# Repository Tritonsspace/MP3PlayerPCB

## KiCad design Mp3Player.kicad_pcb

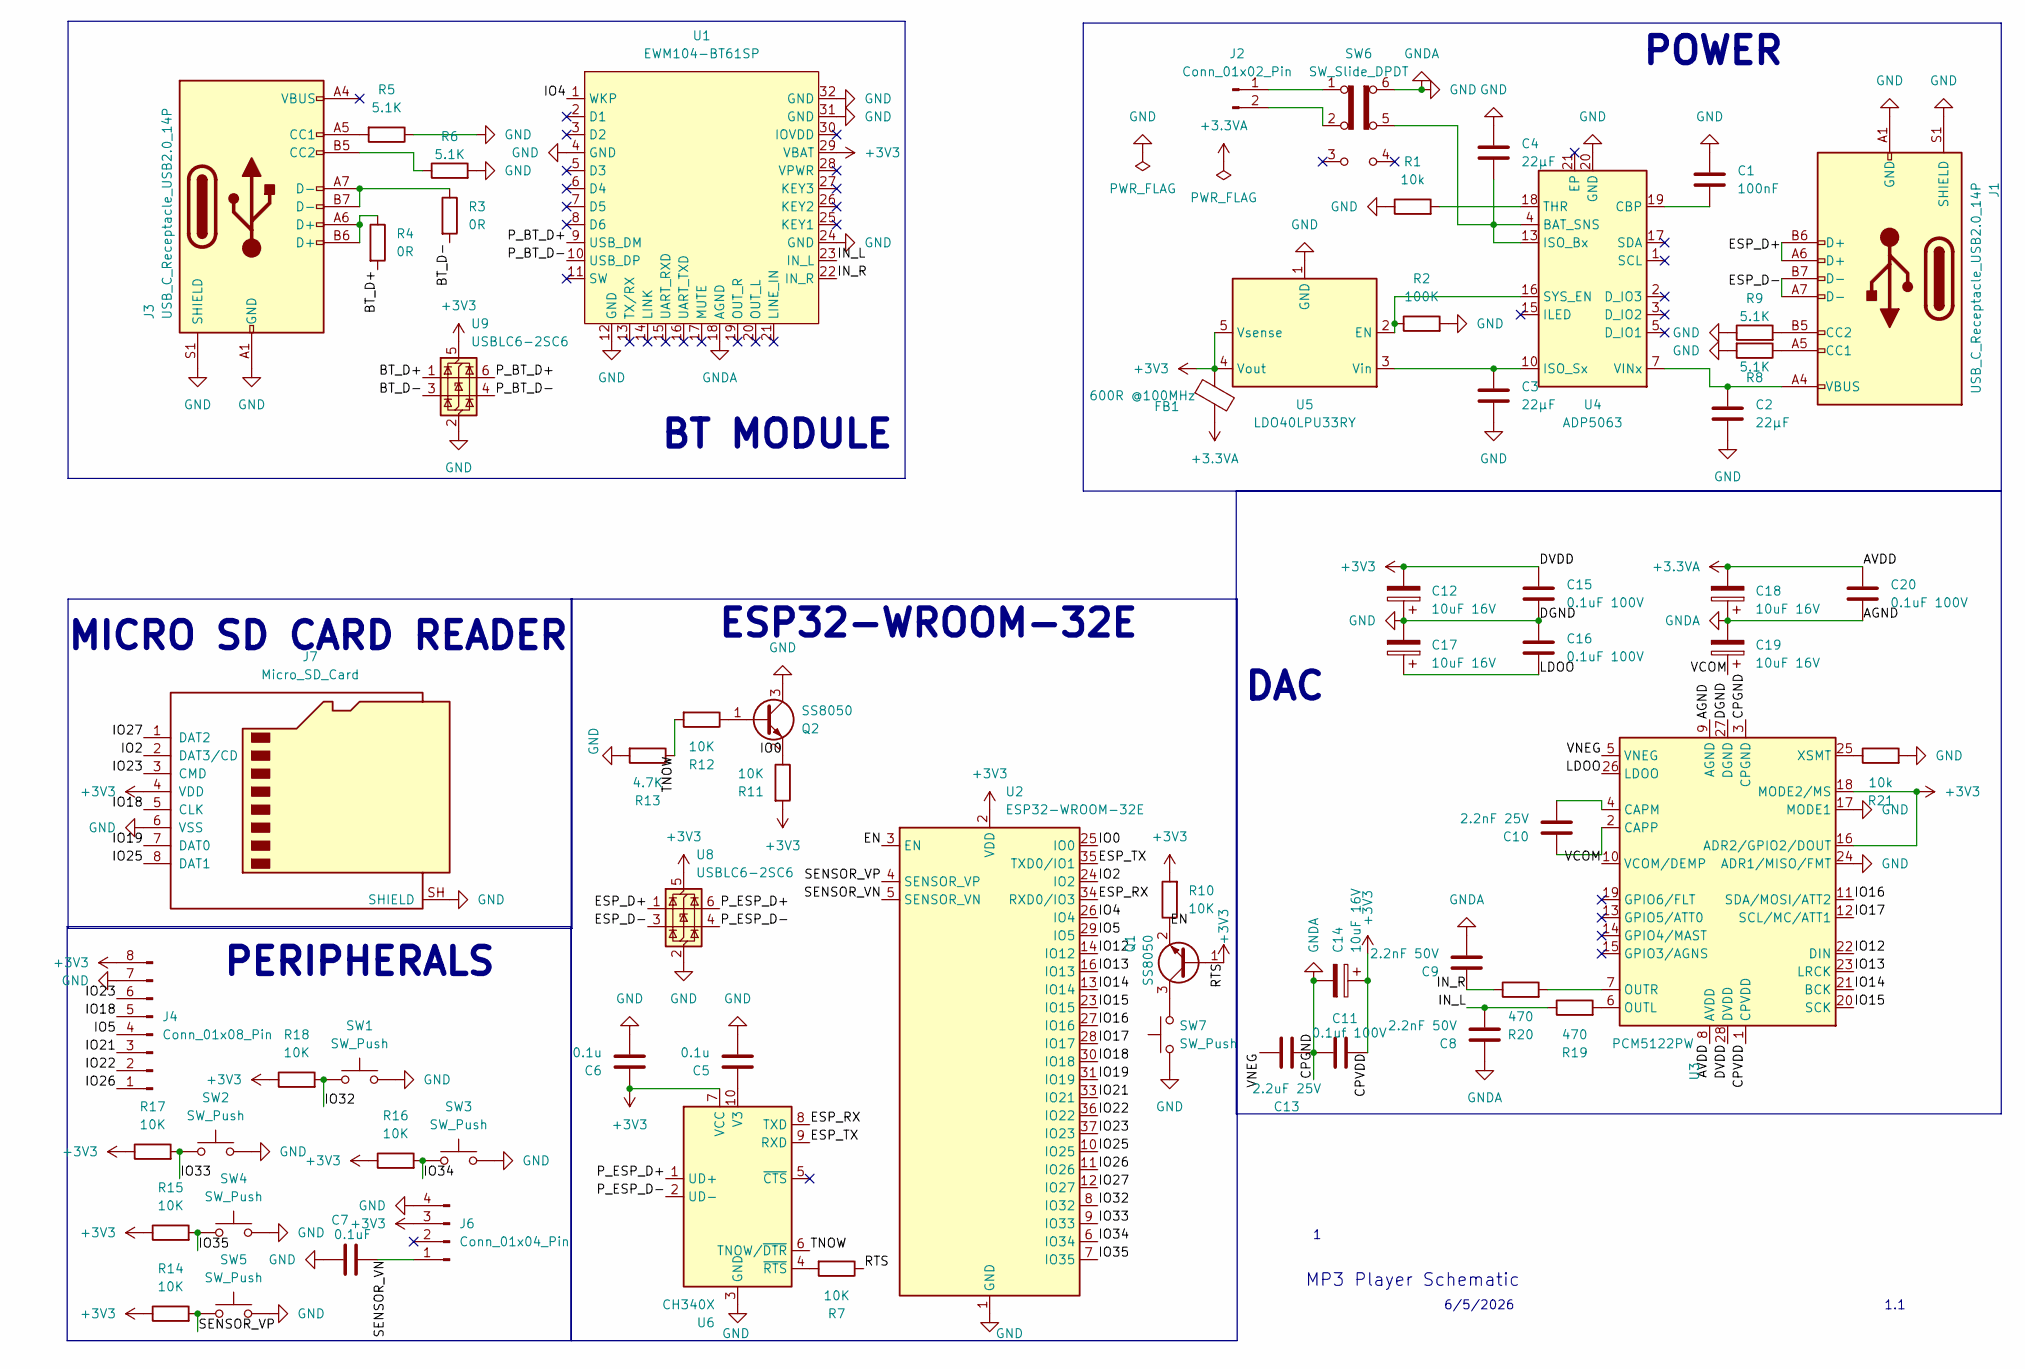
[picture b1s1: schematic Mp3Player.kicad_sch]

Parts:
C1: 100nF; C_0603_1608Metric_Pad1.08x0.95mm_HandSolder
C2, C3, C4: 22µF; C_0603_1608Metric_Pad1.08x0.95mm_HandSolder
C5, C6: 0.1u; C_0603_1608Metric_Pad1.08x0.95mm_HandSolder
C7: 0.1uF; C_0603_1608Metric_Pad1.08x0.95mm_HandSolder
C8, C9: 2.2nF 50V; C_0603_1608Metric_Pad1.08x0.95mm_HandSolder
C10: 2.2nF 25V; C_0603_1608Metric_Pad1.08x0.95mm_HandSolder
C11: 0.1uf 100V; C_0603_1608Metric_Pad1.08x0.95mm_HandSolder
C12, C14, C17, C18, C19: 10uF 16V; C_0603_1608Metric_Pad1.08x0.95mm_HandSolder
C13: 2.2uF 25V; C_0603_1608Metric_Pad1.08x0.95mm_HandSolder
C15, C16, C20: 0.1uF 100V; C_0603_1608Metric_Pad1.08x0.95mm_HandSolder
FB1: 600R @100MHz; R_0603_1608Metric_Pad0.98x0.95mm_HandSolder
J1, J3: USB_C_Receptacle_USB2.0_14P; USB_C_Receptacle_GCT_USB4105-xx-A_16P_TopMnt_Horizontal
J2: Conn_01x02_Pin; JST_PH_S2B-PH-K_1x02_P2.00mm_Horizontal
J4: Conn_01x08_Pin; PinHeader_1x08_P2.54mm_Horizontal
J6: Conn_01x04_Pin; PinHeader_1x04_P2.54mm_Horizontal
J7: Micro_SD_Card; microSD_HC_Hirose_DM3AT-SF-PEJM5
Q1, Q2: SS8050; SOT-23
R1, R21: 10k; R_0603_1608Metric_Pad0.98x0.95mm_HandSolder
R2: 100K; R_0603_1608Metric_Pad0.98x0.95mm_HandSolder
R3, R4: 0R; R_0603_1608Metric_Pad0.98x0.95mm_HandSolder
R5, R6, R8, R9: 5.1K; R_0603_1608Metric_Pad0.98x0.95mm_HandSolder
R7, R10, R11, R12, R14, R15, R16, R17, R18: 10K; R_0603_1608Metric_Pad0.98x0.95mm_HandSolder
R13: 4.7K; R_0603_1608Metric_Pad0.98x0.95mm_HandSolder
R19, R20: 470; R_0603_1608Metric_Pad0.98x0.95mm_HandSolder
SW1, SW2, SW3, SW4, SW5, SW7: SW_Push; SW_Push_1P1T_NO_CK_KMR2
SW6: SW_Slide_DPDT; SW_DPDT_CK_JS202011JCQN
U1: EWM104-BT61SP
U2: ESP32-WROOM-32E; ESP32-WROOM-32D
U3: PCM5122PW; TSSOP-28_4.4x9.7mm_P0.65mm
U4: ADP5063; QFN-20-1EP_4x4mm_P0.5mm_EP2.5x2.5mm
U5: LDO40LPU33RY; DFN-6-1EP_3x3mm_P0.95mm_EP1.7x2.6mm
U6: CH340X; MSOP-10_3x3mm_P0.5mm
U8, U9: USBLC6-2SC6; SOT-23-6

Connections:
+3.3VA: C18.2, C20.1, FB1.2, U3.8 (AVDD)
+3V3: C6.1, C11.2, C12.2, C14.1, C15.1, FB1.1, J4.8, J6.3, J7.4 (VDD), Q1.1 (B), R7.1, R10.2, R11.2, R14.1, R15.1, R16.1, R17.1, R18.1, U1.29 (VBAT), U2.2 (VDD), U3.1 (CPVDD), U3.16 (ADR2/GPIO2/DOUT), U3.18 (MODE2/MS), U3.28 (DVDD), U5.4 (Vout), U5.5 (Vsense), U6.7 (VCC), U8.5 (VBUS), U9.5 (VBUS)
/BT_D+: R4.2, U9.1 (I/O1)
/BT_D-: R3.2, U9.3 (I/O2)
/EN: Q1.2 (E), R10.1, U2.3 (EN)
/ESP_D+: J1.A6 (D+), J1.B6 (D+), U8.1 (I/O1)
/ESP_D-: J1.A7 (D-), J1.B7 (D-), U8.3 (I/O2)
/ESP_RX: U2.34 (RXD0/IO3), U6.8 (TXD)
/ESP_TX: U2.35 (TXD0/IO1), U6.9 (RXD)
/IN_L: C8.2, R19.1, U1.23 (IN_L)
/IN_R: C9.2, R20.1, U1.22 (IN_R)
/IO0: Q2.2 (E), R11.1, U2.25 (IO0)
/IO2: J7.2 (DAT3/CD), U2.24 (IO2)
/IO4: U1.1 (WKP), U2.26 (IO4)
/IO5: J4.4, U2.29 (IO5)
/IO12: U2.14 (IO12), U3.22 (DIN)
/IO13: U2.16 (IO13), U3.23 (LRCK)
/IO14: U2.13 (IO14), U3.21 (BCK)
/IO15: U2.23 (IO15), U3.20 (SCK)
/IO16: U2.27 (IO16), U3.11 (SDA/MOSI/ATT2)
/IO17: U2.28 (IO17), U3.12 (SCL/MC/ATT1)
/IO18: J4.5, J7.5 (CLK), U2.30 (IO18)
/IO19: J7.7 (DAT0), U2.31 (IO19)
/IO21: J4.3, U2.33 (IO21)
/IO22: J4.2, U2.36 (IO22)
/IO23: J4.6, J7.3 (CMD), U2.37 (IO23)
/IO25: J7.8 (DAT1), U2.10 (IO25)
/IO26: J4.1, U2.11 (IO26)
/IO27: J7.1 (DAT2), U2.12 (IO27)
/IO32: R18.2, SW1.1, U2.8 (IO32)
/IO33: R17.2, SW2.1, U2.9 (IO33)
/IO34: R16.2, SW3.1, U2.6 (IO34)
/IO35: R15.2, SW4.1, U2.7 (IO35)
/LDOO: C16.2, C17.1, U3.26 (LDOO)
/P_BT_D+: U1.9 (USB_DM), U9.6 (I/O1)
/P_BT_D-: U1.10 (USB_DP), U9.4 (I/O2)
/P_ESP_D+: U6.1 (UD+), U8.6 (I/O1)
/P_ESP_D-: U6.2 (UD-), U8.4 (I/O2)
/SENSOR_VN: C7.2, J6.1, U2.5 (SENSOR_VN)
/SENSOR_VP: R14.2, SW5.1, U2.4 (SENSOR_VP)
/TNOW: R12.2, R13.1, U6.6 (TNOW/~DTR)
/VCOM: C19.1, U3.10 (VCOM/DEMP)
/VNEG: C13.2, U3.5 (VNEG)
GND: C1.1, C2.2, C3.2, C4.1, C5.2, C6.2, C7.1, C8.1, C9.1, C11.1, C12.1, C13.1, C14.2, C15.2, C16.1, C17.2, C18.1, C19.2, C20.2, J1.A1 (GND), J1.A12 (GND), J1.B1 (GND), J1.B12 (GND), J1.S1 (SHIELD), J3.A1 (GND), J3.A12 (GND), J3.B1 (GND), J3.B12 (GND), J3.S1 (SHIELD), J4.7, J6.4, J7.6 (VSS), J7.SH (SHIELD), Q2.3 (C), R1.1, R2.2, R5.1, R6.2, R8.2, R9.1, R13.2, R21.2, SW1.2, SW2.2, SW3.2, SW4.2, SW5.2, SW6.6 (C), SW7.1, U1.4 (GND), U1.12 (GND), U1.18 (AGND), U1.24 (GND), U1.31 (GND), U1.32 (GND), U2.1 (GND), U2.15 (GND), U2.38 (GND), U2.39 (GND), U3.3 (CPGND), U3.9 (AGND), U3.17 (MODE1), U3.24 (ADR1/MISO/FMT), U3.27 (DGND), U4.20 (GND), U5.1 (GND), U5.7 (GND), U6.3 (GND), U8.2 (GND), U9.2 (GND)
unnamed: C2.1, J1.A4 (VBUS), J1.A9 (VBUS), J1.B4 (VBUS), J1.B9 (VBUS), U4.6 (VINx), U4.7 (VINx), U4.8 (VINx)
unnamed: J1.A5 (CC1), R8.1
unnamed: J1.B5 (CC2), R9.2
unnamed: J2.1, SW6.1 (A)
unnamed: J2.2, SW6.2 (B)
unnamed: J3.A5 (CC1), R5.2
unnamed: J3.B5 (CC2), R6.1
unnamed: J3.A6 (D+), J3.B6 (D+), R4.1
unnamed: J3.A7 (D-), J3.B7 (D-), R3.1
unnamed: Q1.3 (C), SW7.2
unnamed: Q2.1 (B), R12.1
unnamed: C10.2, U3.4 (CAPM)
unnamed: C10.1, U3.2 (CAPP)
unnamed: R19.2, U3.6 (OUTL)
unnamed: R20.2, U3.7 (OUTR)
unnamed: R21.1, U3.25 (XSMT)
unnamed: C4.2, SW6.5 (B), U4.4 (BAT_SNS), U4.12 (ISO_Bx), U4.13 (ISO_Bx), U4.14 (ISO_Bx)
unnamed: C1.2, U4.19 (CBP)
unnamed: R2.1, U4.16 (SYS_EN), U5.2 (EN)
unnamed: R1.2, U4.18 (THR)
unnamed: C3.1, U4.9 (ISO_Sx), U4.10 (ISO_Sx), U4.11 (ISO_Sx), U5.3 (Vin)
unnamed: C5.1, U6.10 (V3)
unnamed: R7.2, U6.4 (~RTS)

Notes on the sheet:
DAC
POWER
BT MODULE
ESP32-WROOM-32E
1.1
MP3 Player Schematic
6/5/2026
MICRO SD CARD READER
PERIPHERALS

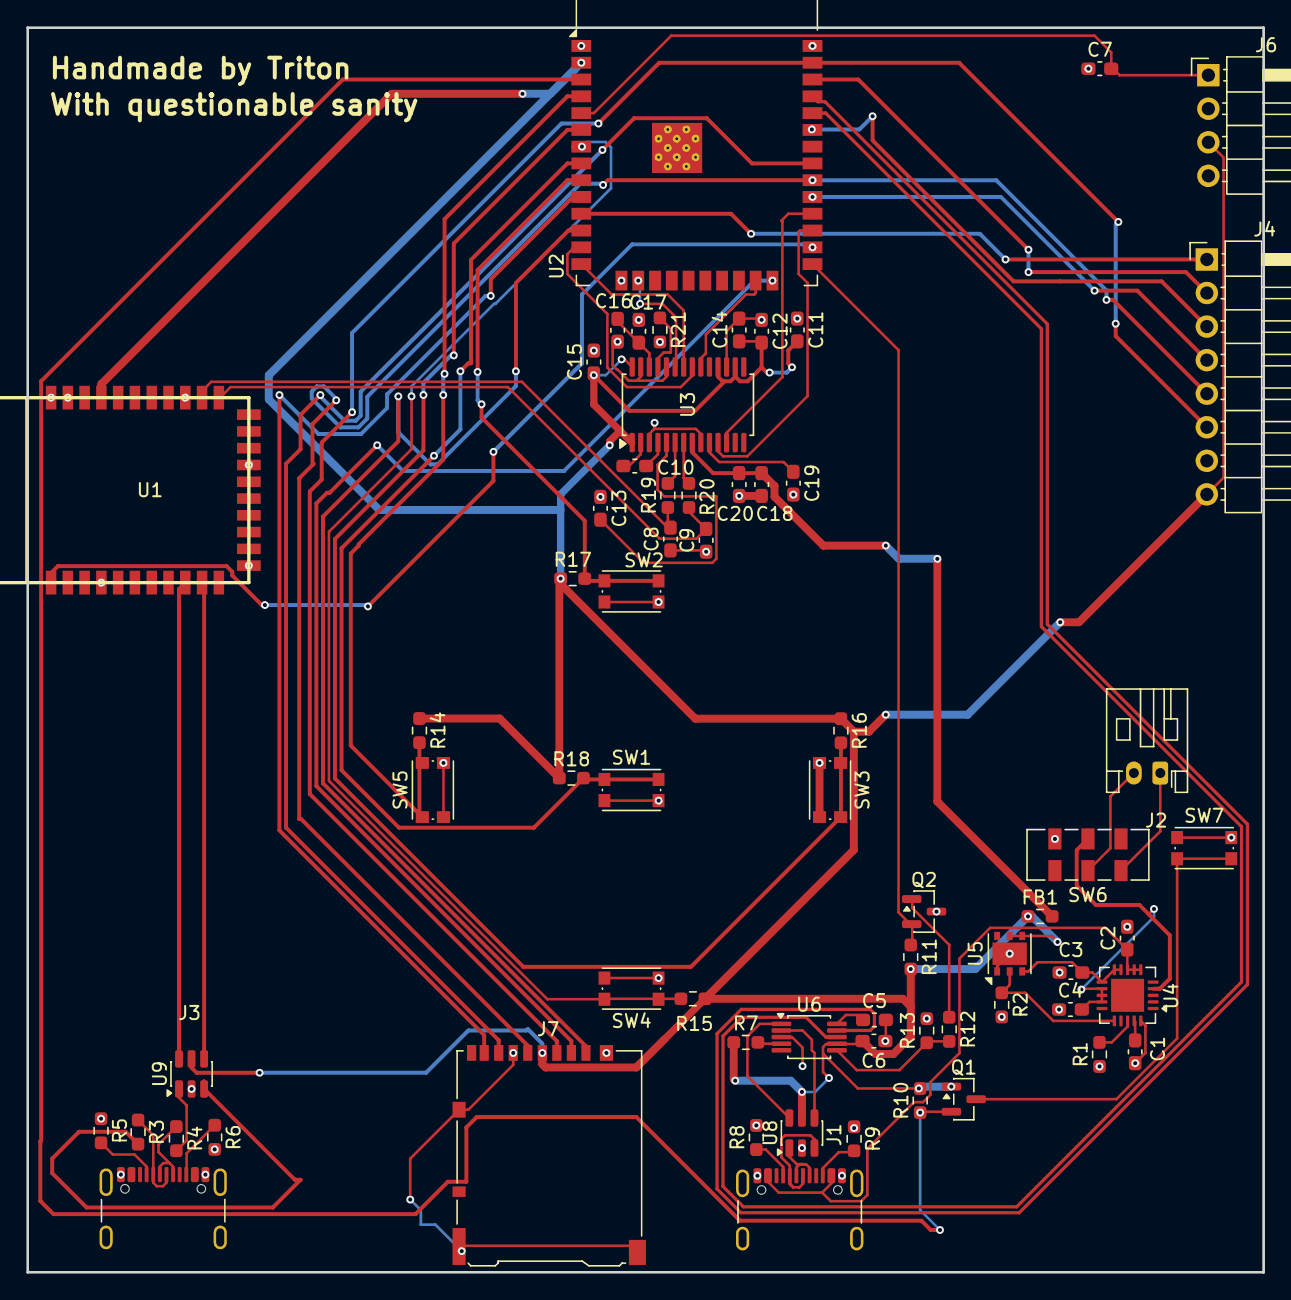
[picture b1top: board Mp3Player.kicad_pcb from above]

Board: 2 copper layers, 93.5 x 94.2 mm, 65 parts (0 on the bottom side), 67 nets.

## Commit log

2026-05-31 Did MP3 Player PCB
